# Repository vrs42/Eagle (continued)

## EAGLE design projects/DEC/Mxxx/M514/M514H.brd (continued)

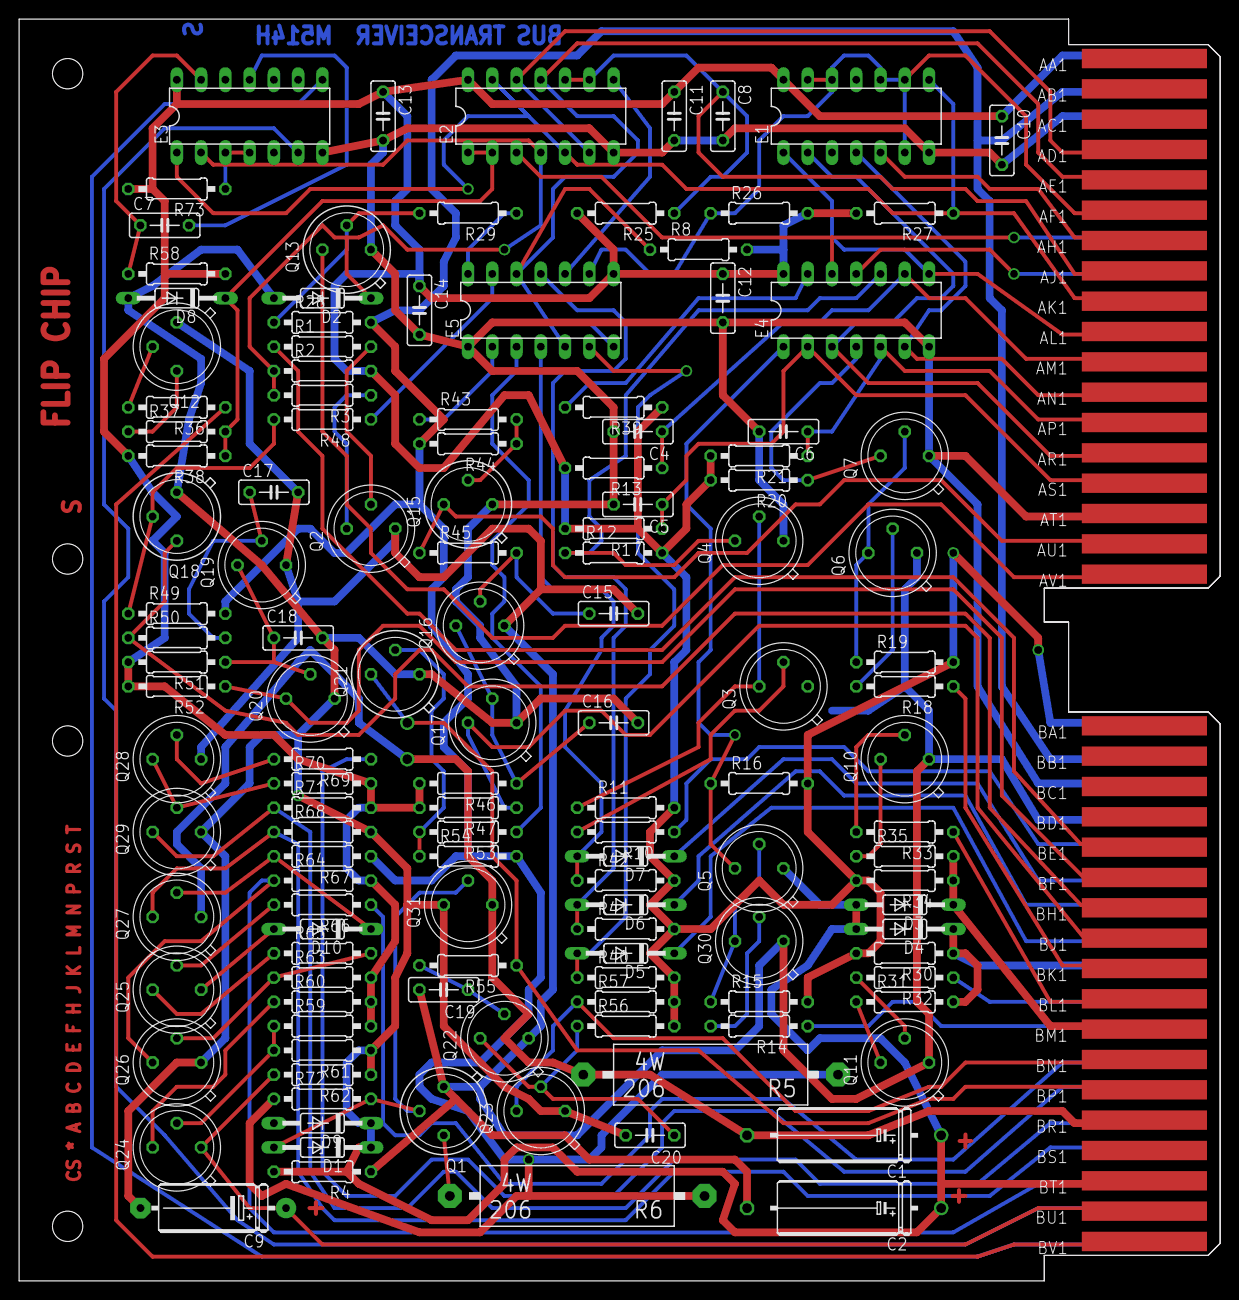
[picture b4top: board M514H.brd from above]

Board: 2 copper layers, 125.7 x 132.1 mm, 133 parts (0 on the bottom side), 98 nets.

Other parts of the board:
U$4: FLIPCHIP

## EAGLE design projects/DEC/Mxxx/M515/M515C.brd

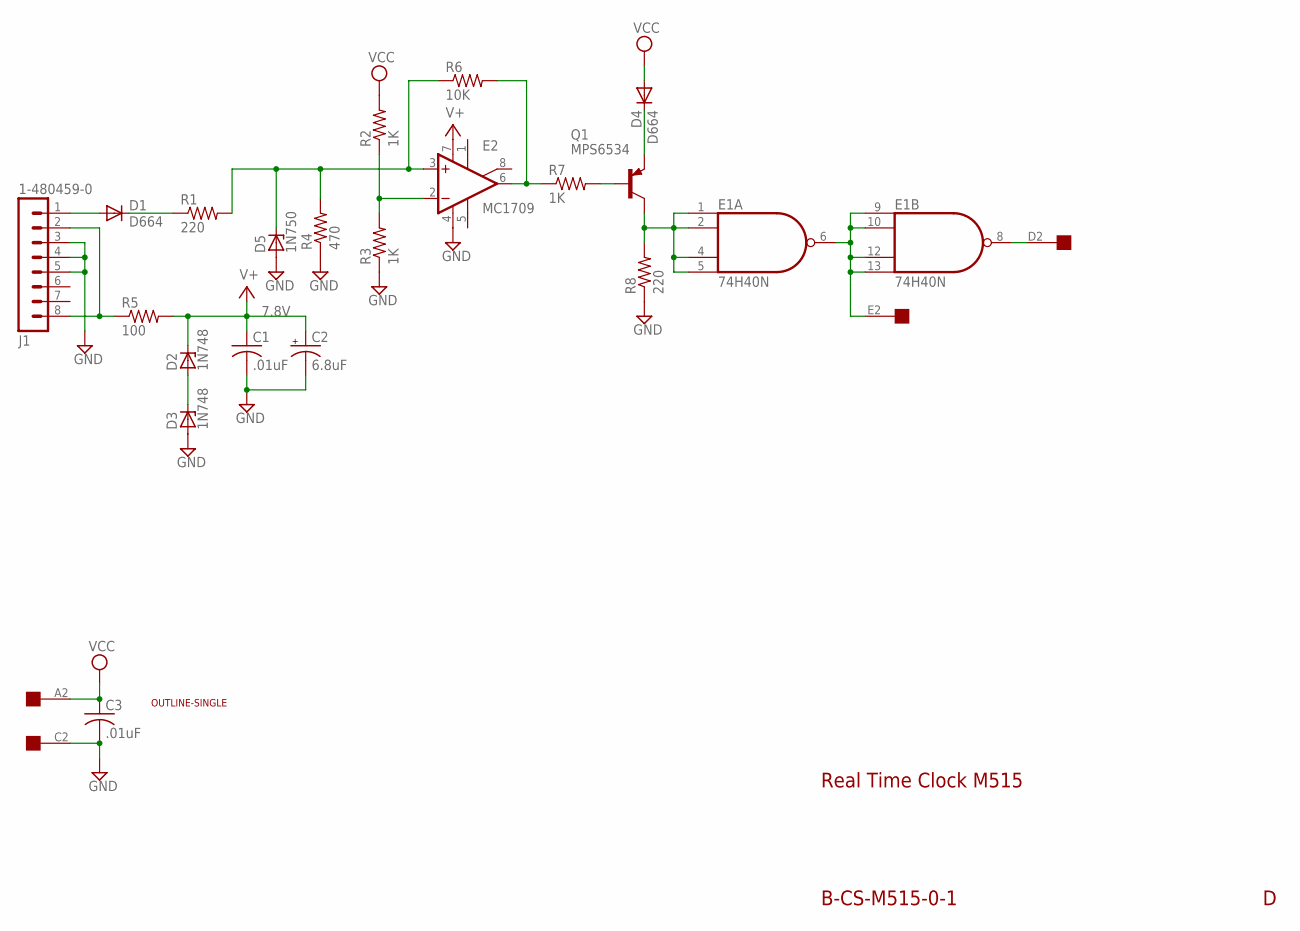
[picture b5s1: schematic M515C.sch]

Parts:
C1, C3: .01uF; C050-025X075
C2: 6.8uF; E12-8
D1, D4: D664; DO35-10
D2, D3: 1N748; DO35Z10
D5: 1N750; DO35Z10
E1: 74H40N; DIL14
E2: MC1709; H08C
J1: 1-480459-0
Q1: MPS6534; TO5
R1, R8: 220; 0207/10
R2, R3, R7: 1K; 0207/10
R4: 470; 0207/10
R5: 100; 0207/10
R6: 10K; 0207/10
U$1: OUTLINE-SINGLE; SINGLE
U$3: EDGE-1; EDGE-CON1

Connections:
GND: C1.2, C2.-, C3.2, D3.A, D5.A, E1.7 (GND), E2.4 (V-), J1.3, J1.4, J1.5, R3.1, R4.1, R8.1, U$3.C2
unnamed: D1.A, J1.1
unnamed: D2.A, D3.C
unnamed: J1.2, J1.8, R5.1
unnamed: D1.C, R1.1
unnamed: D5.C, E2.3 (+IN), R1.2, R4.2, R6.1
unnamed: E1.8 (O), U$3.D2
unnamed: E1.6 (O), E1.9 (I0), E1.10 (I1), E1.12 (I2), E1.13 (I3), U$3.E2
unnamed: E1.1 (I0), E1.2 (I1), E1.4 (I2), E1.5 (I3), Q1.3 (C), R8.2
unnamed: D4.C, Q1.1 (E)
unnamed: Q1.2 (B), R7.2
unnamed: E2.6 (OUT), R6.2, R7.1
unnamed: E2.2 (-IN), R2.1, R3.2
V+: C1.1, C2.+, D2.C, E2.7 (V+), R5.2
VCC: C3.1, D4.A, E1.14 (VCC), R2.2, U$3.A2

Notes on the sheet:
7.8V
B-CS-M515-0-1
Real Time Clock M515

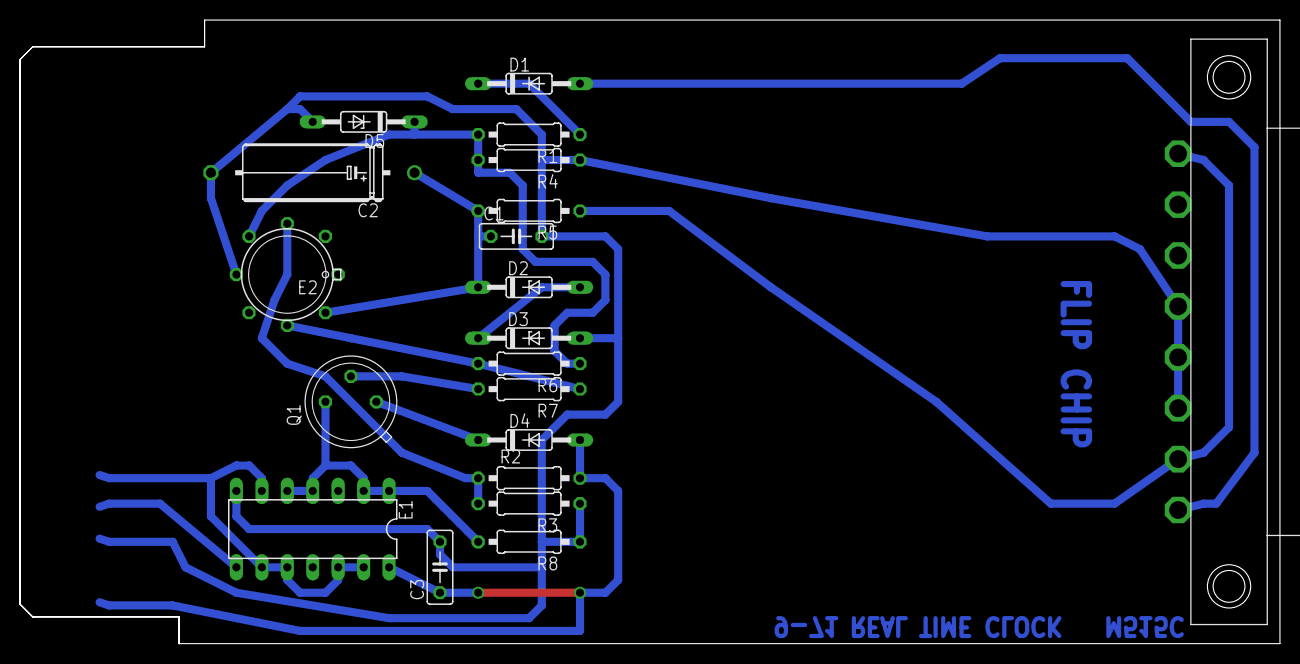
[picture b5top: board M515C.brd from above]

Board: 2 copper layers, 125.7 x 62.2 mm, 22 parts (0 on the bottom side), 15 nets.
